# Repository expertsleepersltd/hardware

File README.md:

Please see individual folders for licensing information.

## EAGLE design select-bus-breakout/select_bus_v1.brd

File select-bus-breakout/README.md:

Select Bus Breakout
=====

https://www.expert-sleepers.co.uk/selectbusbreakout.html

Copyright (c) 2018 Expert Sleepers Ltd

Please refer to [LICENSE.md](LICENSE.md) for licensing information.

Please note that Expert Sleepers® is a registered trade mark in the UK. Remove any branding before making a derivative work.

Front panel layout is [here](../panels).

Board and schematic are in [EAGLE](https://en.wikipedia.org/wiki/EAGLE_(program)) format.

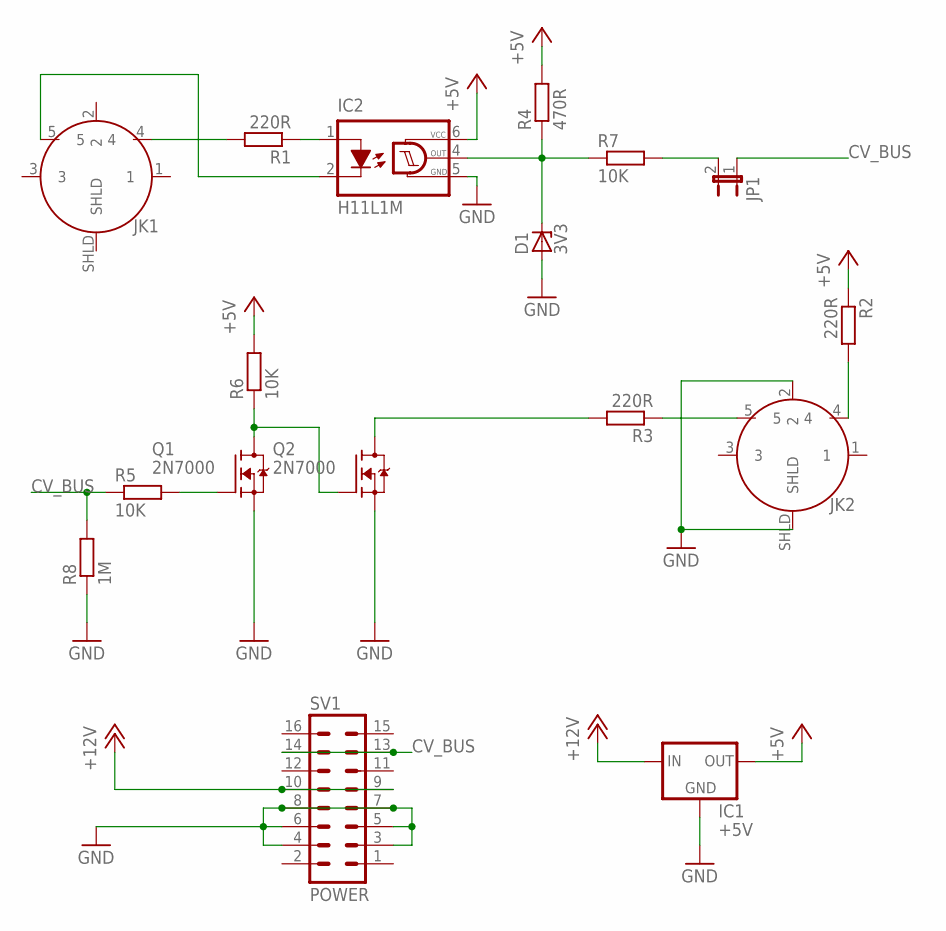
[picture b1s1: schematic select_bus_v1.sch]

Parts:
D1: 3V3; DO41Z10
IC1: +5V; 78LXX
IC2: H11L1M; DIL06
JK1, JK2: 13HP021PCB
JP1: JP1E; JP1
Q1, Q2: 2N7000; TO92
R1, R2, R3: 220R; 0207/10
R4: 470R; 0207/10
R5, R6: 10K; 0207/10
R7: 10K; 0207/2V
R8: 1M; 0207/10
SV1: POWER; ML16

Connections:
+5V: IC1.OUT, IC2.6 (VCC), R2.1, R4.2, R6.2
+12V: IC1.IN, SV1.9, SV1.10
CV_BUS: JP1.1, R5.1, R8.2, SV1.13, SV1.14
GND: D1.A, IC1.GND, IC2.5 (GND), JK2.2, JK2.SHLD, Q1.1 (S), Q2.1 (S), R8.1, SV1.3, SV1.4, SV1.5, SV1.6, SV1.7, SV1.8
unnamed: JP1.2, R7.2
unnamed: JK2.5, R3.1
unnamed: JK1.4, R1.2
unnamed: Q2.3 (D), R3.2
unnamed: JK2.4, R2.2
unnamed: IC2.1 (A), R1.1
unnamed: IC2.2 (C), JK1.5
unnamed: Q1.2 (G), R5.2
U1RX: D1.C, IC2.4 (OUT), R4.1, R7.1
U1TX: Q1.3 (D), Q2.2 (G), R6.1

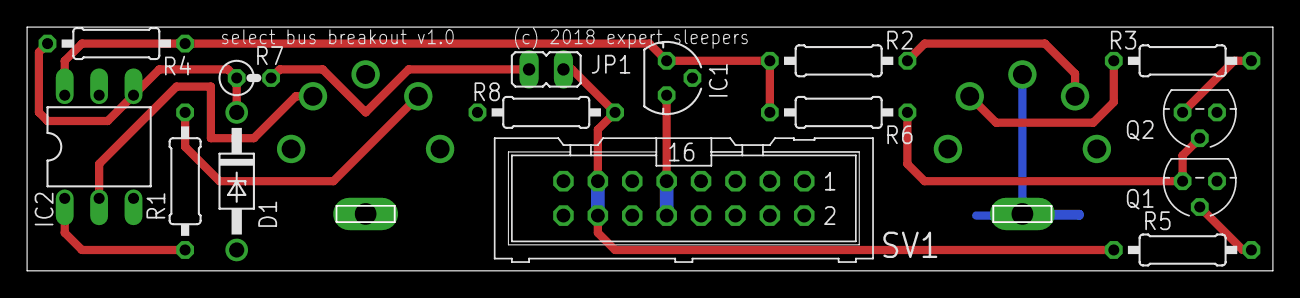
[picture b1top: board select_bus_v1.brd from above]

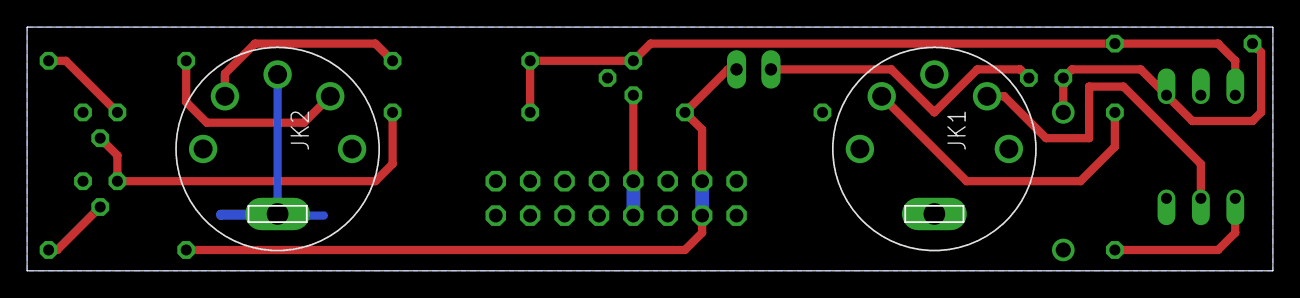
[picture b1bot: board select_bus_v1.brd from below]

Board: 2 copper layers, 91.9 x 17.9 mm, 17 parts (2 on the bottom side), 14 nets.

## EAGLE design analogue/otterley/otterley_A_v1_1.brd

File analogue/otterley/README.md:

Otterley
=====

https://expert-sleepers.co.uk/otterley.html

Copyright (c) 2024 Expert Sleepers Ltd

Please refer to [LICENSE.md](LICENSE.md) for licensing information.

Please note that Expert Sleepers® is a registered trade mark in the UK, the European Union, and the United States. Remove any branding before making a derivative work.

Front panel layout is [here](../../panels).

Board and schematic are in [EAGLE](https://en.wikipedia.org/wiki/EAGLE_(program)) format.

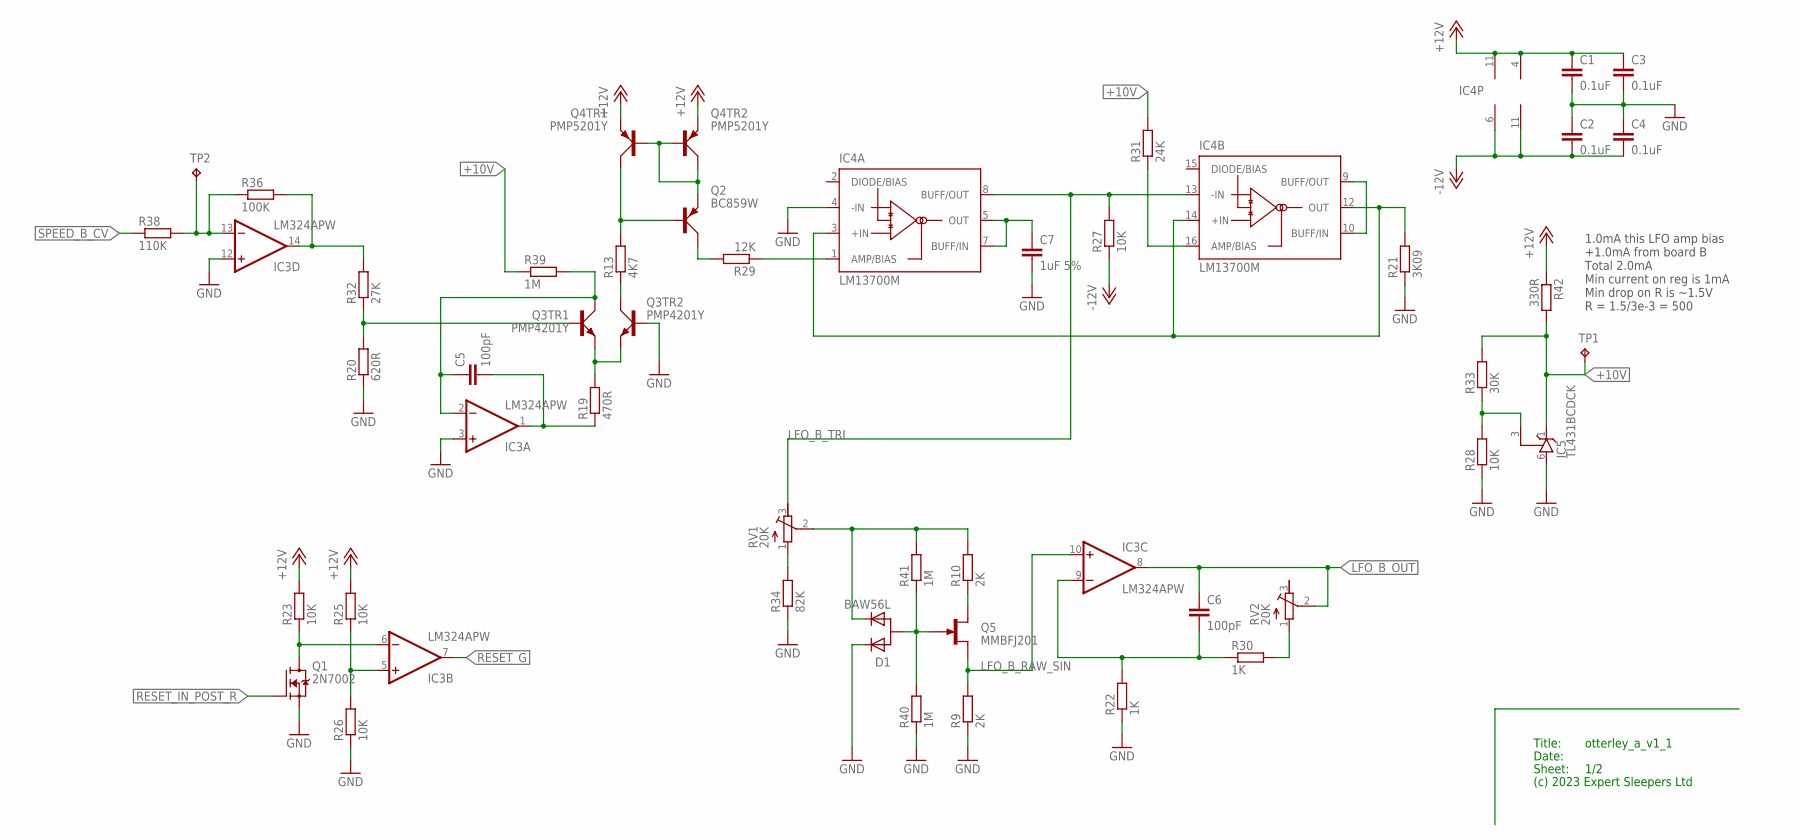
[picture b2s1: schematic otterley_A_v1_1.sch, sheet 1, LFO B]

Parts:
C1, C2, C3, C4: 0.1uF; C0402
C5, C6: 100pF; C0603
C7: 1uF 5%; C0805
D1: BAW56L; SOT-23
IC3: LM324APW; PW_R-PDSO-G14
IC4: LM13700M; SO16
IC5: TL431BCDCK; DCK_SC-70
Q1: 2N7002; SOT23
Q2: BC859W; SOT323
Q3: PMP4201Y; SOT65P210X110-6N
Q4: PMP5201Y; SOT65P210X110-6N
Q5: MMBFJ201; SOT23
R9, R10: 2K; R1206
R13: 4K7; R1206
R19: 470R; R1206
R20: 620R; R0603
R21: 3K09; R0603
R22, R30: 1K; R0603
R23, R25, R26, R27, R28: 10K; R0603
R29: 12K; R0603
R31: 24K; R0603
R32: 27K; R0603
R33: 30K; R0603
R34: 82K; R0603
R36: 100K; R0603
R38: 110K; R0603
R39, R40, R41: 1M; R0603
R42: 330R; R1206
RV1, RV2: 20K; 3306_W
TP1, TP2: RA2; P1-13

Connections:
+10V: IC5.1 (C), R31.2, R33.2, R39.1, R42.2, TP1.TP; also elsewhere on the board
+12V: C1.1, C3.1, IC3.4 (V+), IC4.11 (V+), Q4.4 (E), Q4.5 (E), R23.2, R25.2, R42.1; also elsewhere on the board
-12V: C2.2, C4.2, IC3.11 (V-), IC4.6 (V-), R27.1; also elsewhere on the board
GND: C1.2, C2.1, C3.2, C4.1, C7.2, D1.1 (C1), IC3.3 (+IN), IC3.12 (+IN), IC4.4 (-IN), IC5.6 (A), Q1.2 (S), Q3.2 (B), R9.1, R20.1, R21.1, R22.1, R26.1, R28.1, R34.1, R40.1; also elsewhere on the board
LFO_B_OUT: C6.1, IC3.8 (OUT), RV2.2 (S); also elsewhere on the board
LFO_B_RAW_SIN: IC3.10 (+IN), Q5.2 (S), R9.2
LFO_B_TRI: IC4.8 (BUFF/OUT), IC4.13 (-IN), R27.2, RV1.3 (E)
unnamed: IC5.3 (R), R28.2, R33.1
unnamed: IC3.6 (-IN), Q1.3 (D), R23.1
unnamed: IC3.5 (+IN), R25.1, R26.2
unnamed: IC3.14 (OUT), R32.2, R36.2
unnamed: IC4.9 (BUFF/OUT), IC4.10 (BUFF/IN)
unnamed: C7.1, IC4.5 (OUT), IC4.7 (BUFF/IN)
unnamed: IC4.3 (+IN), IC4.12 (OUT), IC4.14 (+IN), R21.2
unnamed: IC4.16 (AMP/BIAS), R31.1
unnamed: IC4.1 (AMP/BIAS), R29.1
unnamed: IC3.13 (-IN), R36.1, R38.2, TP2.TP
unnamed: C5.1, IC3.2 (-IN), Q3.6 (C), R39.2
unnamed: C5.2, IC3.1 (OUT), R19.1
unnamed: Q3.4 (E), Q3.5 (E), R19.2
unnamed: Q3.1 (B), R20.2, R32.1
unnamed: Q2.3 (C), R29.2
unnamed: Q2.1 (B), Q4.6 (C), R13.2
unnamed: Q2.2 (E), Q4.1 (B), Q4.2 (B), Q4.3 (C)
unnamed: Q3.3 (C), R13.1
unnamed: R34.2, RV1.1 (A)
unnamed: D1.2 (C2), R10.2, R41.2, RV1.2 (S)
unnamed: D1.3 (A), Q5.3 (G), R40.2, R41.1
unnamed: Q5.1 (D), R10.1
unnamed: C6.2, IC3.9 (-IN), R22.2, R30.1
unnamed: R30.2, RV2.1 (A)
RESET_G: IC3.7 (OUT); also elsewhere on the board
RESET_IN_POST_R: Q1.1 (G); also elsewhere on the board
SPEED_B_CV: R38.1; also elsewhere on the board

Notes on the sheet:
Title:
Date:
Sheet:
(c) 2023 Expert Sleepers Ltd
1.0mA this LFO amp bias +1.0mA from board B Total 2.0mA Min current on reg is 1mA Min drop on R is ~1.5V R = 1.5/3e-3 = 500

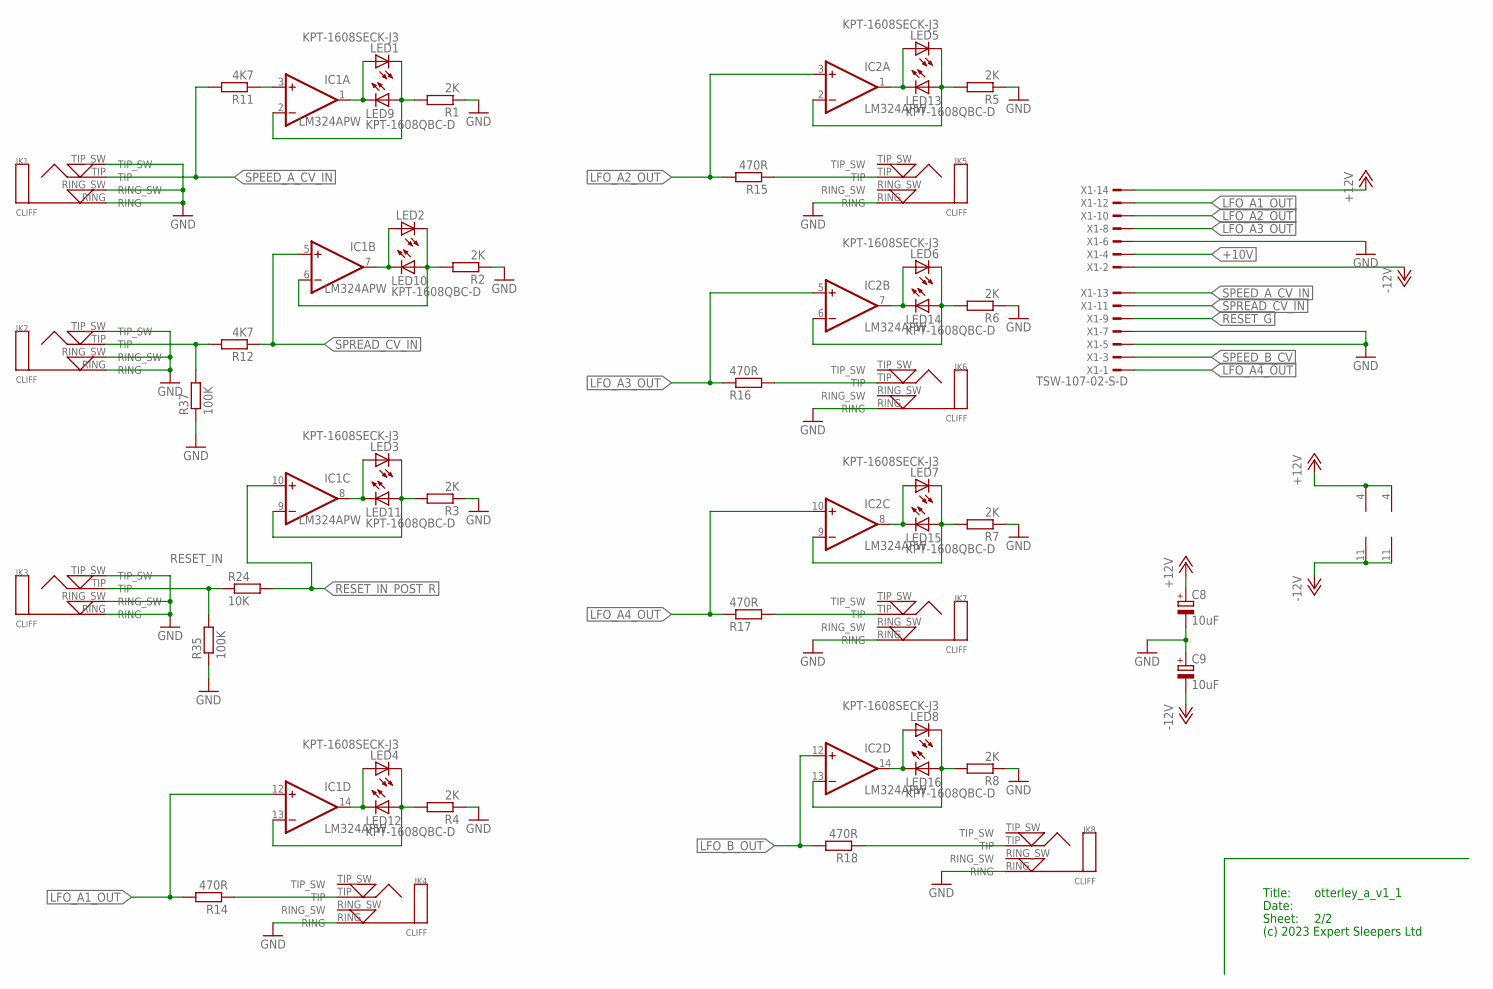
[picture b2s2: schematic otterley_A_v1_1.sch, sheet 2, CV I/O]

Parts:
C8, C9: 10uF; UD-4X5,8_NICHICON
IC1, IC2: LM324APW; PW_R-PDSO-G14
JK1, JK2, JK3, JK4, JK5, JK6, JK7, JK8: CLIFF; CLIFF3.5MMPCB
LED1, LED2, LED3, LED4, LED5, LED6, LED7, LED8: KPT-1608SECK-J3; CHIPLED_0603_LEFT
LED9, LED10, LED11, LED12, LED13, LED14, LED15, LED16: KPT-1608QBC-D; CHIPLED_0603_RIGHT
R1, R2, R3, R4, R5, R6, R7, R8: 2K; R1206
R11, R12: 4K7; R1206
R14, R15, R16, R17, R18: 470R; R1206
R24: 10K; R0603
R35, R37: 100K; R0603
X1: TSW-107-02-S-D

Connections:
+10V: X1.4; also elsewhere on the board
+12V: C8.+, IC1.4 (V+), IC2.4 (V+), X1.14; also elsewhere on the board
-12V: C9.-, IC1.11 (V-), IC2.11 (V-), X1.2; also elsewhere on the board
GND: C8.-, C9.+, JK1.RING, JK1.RING_SW, JK1.TIP_SW, JK2.RING, JK2.RING_SW, JK2.TIP_SW, JK3.RING, JK3.RING_SW, JK3.TIP_SW, JK4.RING, JK5.RING, JK6.RING, JK7.RING, JK8.RING, R1.1, R2.1, R3.1, R4.1, R5.1, R6.1, R7.1, R8.1, R35.1, R37.1, X1.5, X1.6, X1.7; also elsewhere on the board
LFO_A1_JACK: JK4.TIP, R14.1
LFO_A1_OUT: IC1.12 (+IN), R14.2, X1.12
LFO_A2_JACK: JK5.TIP, R15.1
LFO_A2_OUT: IC2.3 (+IN), R15.2, X1.10
LFO_A3_JACK: JK6.TIP, R16.2
LFO_A3_OUT: IC2.5 (+IN), R16.1, X1.8
LFO_A4_JACK: JK7.TIP, R17.2
LFO_A4_OUT: IC2.10 (+IN), R17.1, X1.1
LFO_B_JACK: JK8.TIP, R18.1
LFO_B_OUT: IC2.12 (+IN), R18.2; also elsewhere on the board
unnamed: IC1.13 (-IN), LED4.1 (C), LED12.1 (A), R4.2
unnamed: IC1.14 (OUT), LED4.2 (A), LED12.2 (C)
unnamed: IC2.2 (-IN), LED5.1 (C), LED13.1 (A), R5.2
unnamed: IC1.8 (OUT), LED3.2 (A), LED11.2 (C)
unnamed: JK2.TIP, R12.2, R37.2
unnamed: IC1.9 (-IN), LED3.1 (C), LED11.1 (A), R3.2
unnamed: IC1.1 (OUT), LED1.2 (A), LED9.2 (C)
unnamed: IC1.2 (-IN), LED1.1 (C), LED9.1 (A), R1.2
unnamed: IC1.3 (+IN), R11.1
unnamed: IC1.7 (OUT), LED2.2 (A), LED10.2 (C)
unnamed: IC1.6 (-IN), LED2.1 (C), LED10.1 (A), R2.2
unnamed: IC2.8 (OUT), LED7.2 (A), LED15.2 (C)
unnamed: IC2.9 (-IN), LED7.1 (C), LED15.1 (A), R7.2
unnamed: IC2.14 (OUT), LED8.2 (A), LED16.2 (C)
unnamed: IC2.13 (-IN), LED8.1 (C), LED16.1 (A), R8.2
unnamed: IC2.7 (OUT), LED6.2 (A), LED14.2 (C)
unnamed: IC2.6 (-IN), LED6.1 (C), LED14.1 (A), R6.2
unnamed: IC2.1 (OUT), LED5.2 (A), LED13.2 (C)
RESET_G: X1.9; also elsewhere on the board
RESET_IN: JK3.TIP, R24.1, R35.2
RESET_IN_POST_R: IC1.10 (+IN), R24.2; also elsewhere on the board
SPEED_A_CV_IN: JK1.TIP, R11.2, X1.13
SPEED_B_CV: X1.3; also elsewhere on the board
SPREAD_CV_IN: IC1.5 (+IN), R12.1, X1.11

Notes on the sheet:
Title:
Date:
Sheet:
(c) 2023 Expert Sleepers Ltd

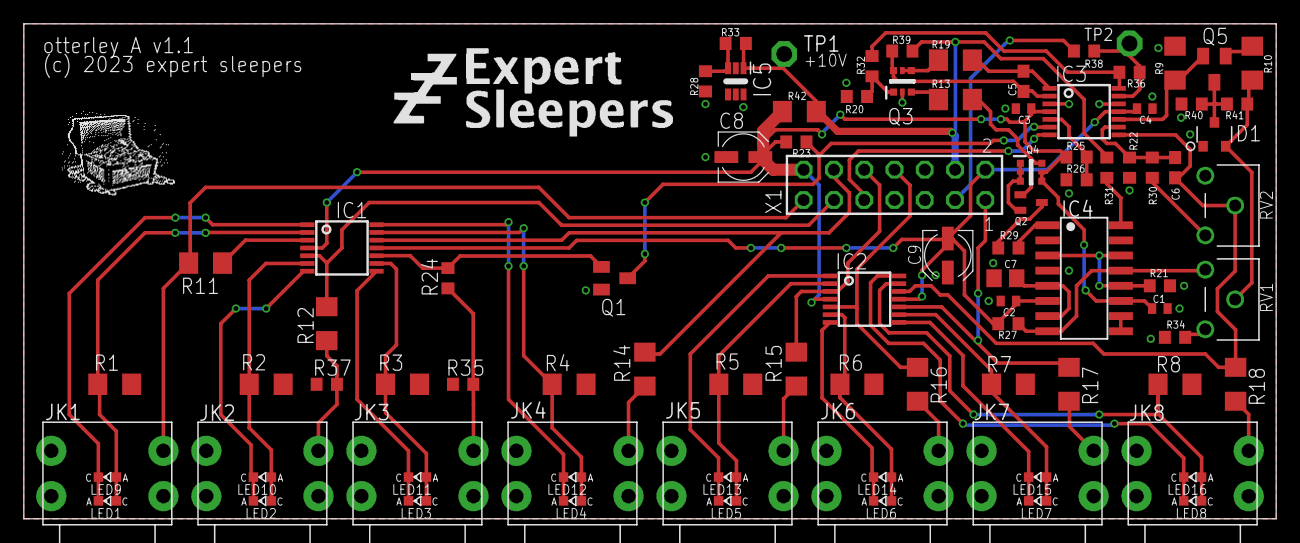
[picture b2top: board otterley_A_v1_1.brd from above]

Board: 2 copper layers, 105.0 x 41.5 mm, 93 parts (0 on the bottom side), 64 nets.

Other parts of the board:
U$1: ES_ZZZ_TEXT_TPLACE_1IN_600DPI
U$2: TREASURE_10MM_300DPI

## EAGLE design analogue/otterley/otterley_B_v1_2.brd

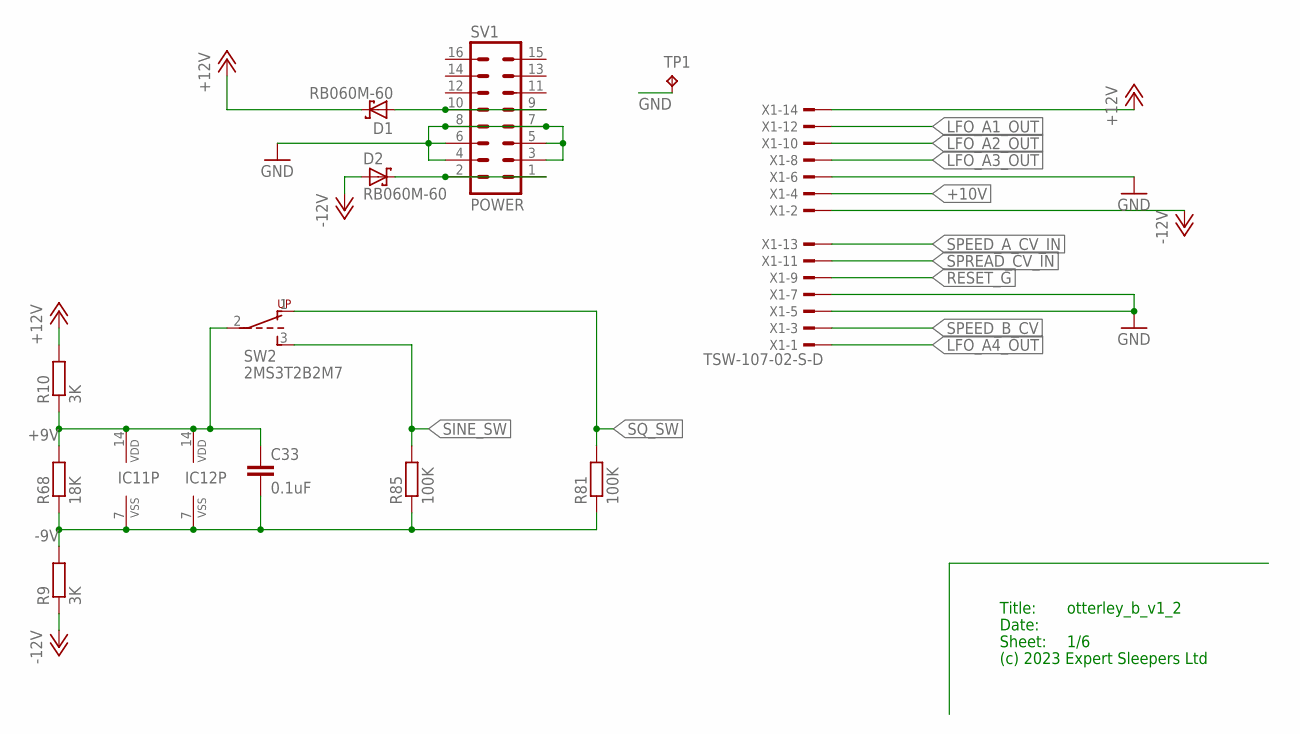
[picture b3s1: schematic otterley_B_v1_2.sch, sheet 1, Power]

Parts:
C33: 0.1uF; C0402
D1, D2: RB060M-60; SOD123FL
IC11, IC12: CD4066BPW; PW_R-PDSO-G14
R9, R10: 3K; R0603
R68: 18K; R0603
R81, R85: 100K; R0603
SV1: POWER; ML16
SW2: 2MS3T2B2M7; 2MS1T2B2M7RE
TP1: RA2; P1-13
X1: TSW-107-02-S-D

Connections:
+9V: C33.1, IC11.14 (VDD), IC12.14 (VDD), R10.1, R68.2, SW2.2 (PR)
+10V: X1.4; also elsewhere on the board
+12V: D1.C, R10.2, X1.14; also elsewhere on the board
-9V: C33.2, IC11.7 (VSS), IC12.7 (VSS), R9.2, R68.1, R81.1, R85.1
-12V: D2.A, R9.1, X1.2; also elsewhere on the board
GND: SV1.3, SV1.4, SV1.5, SV1.6, SV1.7, SV1.8, TP1.TP, X1.5, X1.6, X1.7; also elsewhere on the board
LFO_A1_OUT: X1.12; also elsewhere on the board
LFO_A2_OUT: X1.10; also elsewhere on the board
LFO_A3_OUT: X1.8; also elsewhere on the board
LFO_A4_OUT: X1.1; also elsewhere on the board
unnamed: D2.C, SV1.1, SV1.2
unnamed: D1.A, SV1.9, SV1.10
RESET_G: X1.9; also elsewhere on the board
SINE_SW: R85.2, SW2.3 (RD); also elsewhere on the board
SPEED_A_CV_IN: X1.13; also elsewhere on the board
SPEED_B_CV: X1.3; also elsewhere on the board
SPREAD_CV_IN: X1.11; also elsewhere on the board
SQ_SW: R81.2, SW2.1 (RU); also elsewhere on the board

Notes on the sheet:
Title:
Date:
Sheet:
(c) 2023 Expert Sleepers Ltd

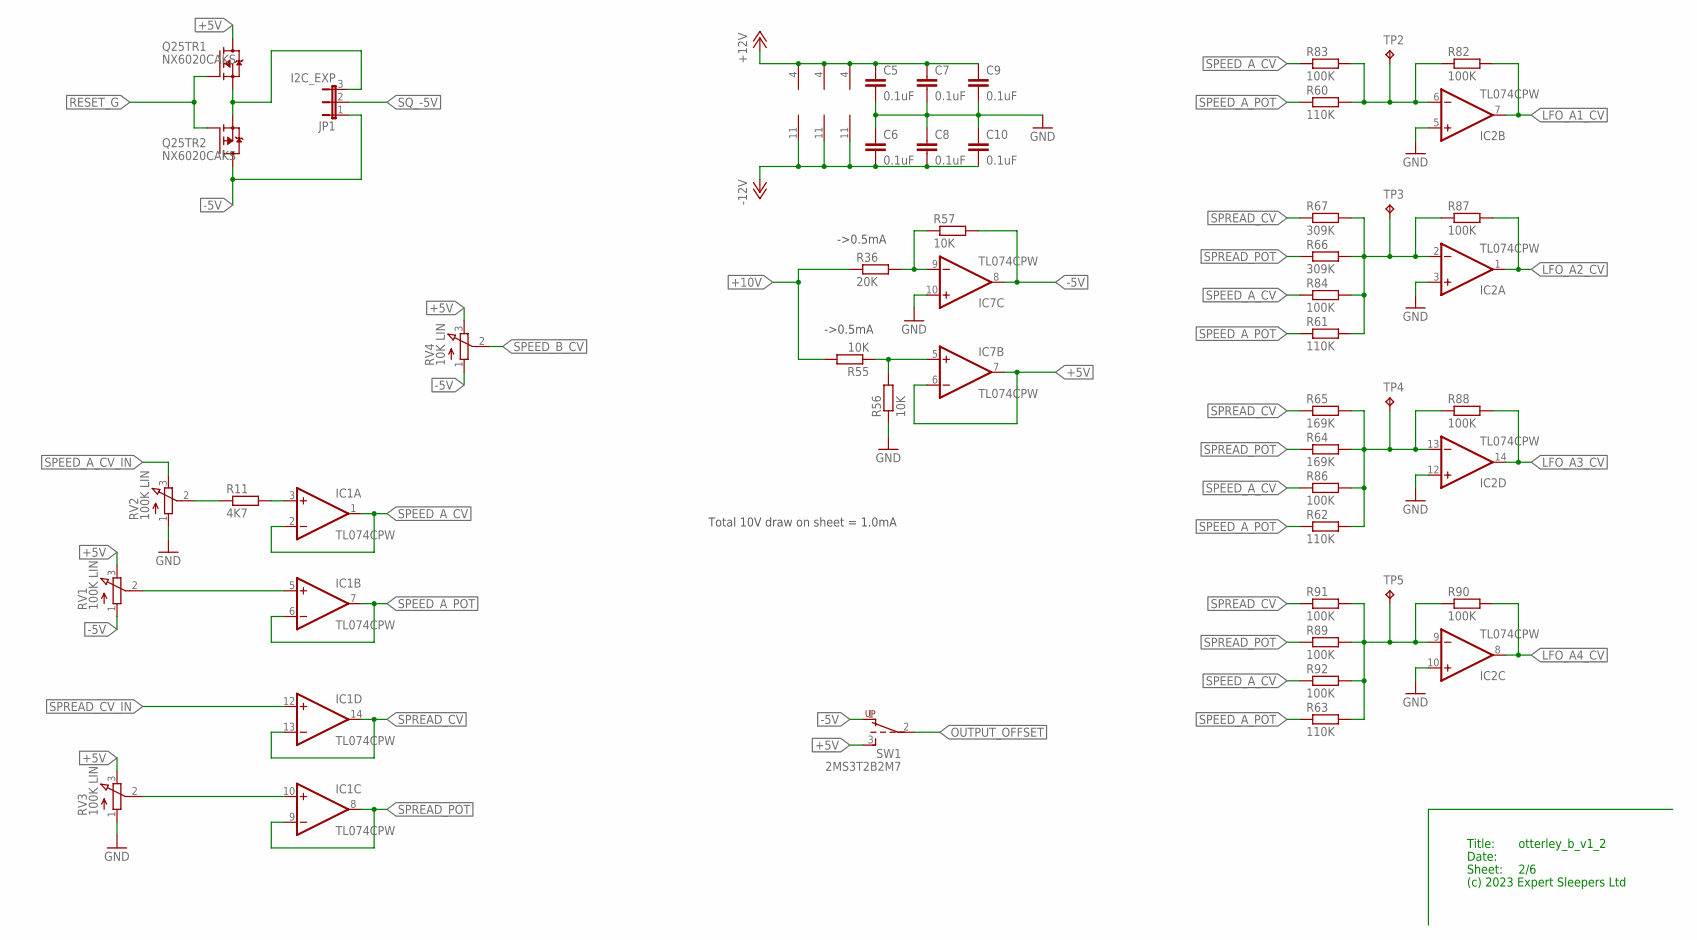
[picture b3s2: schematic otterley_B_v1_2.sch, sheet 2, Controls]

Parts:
C5, C6, C7, C8, C9, C10: 0.1uF; C0402
IC1, IC2, IC7: TL074CPW; PW_R-PDSO-G14
JP1: I2C_EXP; JP2
Q25: NX6020CAKS; SOT363
R11: 4K7; R0603
R36: 20K; R0603
R55, R56, R57: 10K; R0603
R60, R61, R62, R63: 110K; R0603
R64, R65: 169K; R0603
R66, R67: 309K; R0603
R82, R83, R84, R86, R87, R88, R89, R90, R91, R92: 100K; R0603
RV1, RV2, RV3: 100K LIN; RD1610NOA0X
RV4: 10K LIN; RD1610NOA0X
SW1: 2MS3T2B2M7; 2MS1T2B2M7RE
TP2, TP3, TP4, TP5: RA2; P1-13

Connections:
+5V: IC7.6 (-IN), IC7.7 (OUT), Q25.6 (D), RV1.3 (E), RV3.3 (E), RV4.3 (E), SW1.3 (RD); also elsewhere on the board
+10V: R36.1, R55.2; also elsewhere on the board
+12V: C5.1, C7.1, C9.1, IC1.4 (V+), IC2.4 (V+), IC7.4 (V+); also elsewhere on the board
-5V: IC7.8 (OUT), JP1.1, Q25.3 (D), R57.2, RV1.1 (A), RV4.1 (A), SW1.1 (RU)
-12V: C6.2, C8.2, C10.2, IC1.11 (V-), IC2.11 (V-), IC7.11 (V-); also elsewhere on the board
GND: C5.2, C6.1, C7.2, C8.1, C9.2, C10.1, IC2.3 (+IN), IC2.5 (+IN), IC2.10 (+IN), IC2.12 (+IN), IC7.10 (+IN), R56.1, RV2.1 (A), RV3.1 (A); also elsewhere on the board
LFO_A1_CV: IC2.7 (OUT), R82.2; also elsewhere on the board
LFO_A2_CV: IC2.1 (OUT), R87.2; also elsewhere on the board
LFO_A3_CV: IC2.14 (OUT), R88.2; also elsewhere on the board
LFO_A4_CV: IC2.8 (OUT), R90.2; also elsewhere on the board
unnamed: JP1.3, Q25.1 (S), Q25.4 (S)
unnamed: IC1.5 (+IN), RV1.2 (S)
unnamed: R11.1, RV2.2 (S)
unnamed: IC7.5 (+IN), R55.1, R56.2
unnamed: IC7.9 (-IN), R36.2, R57.1
unnamed: IC2.2 (-IN), R61.2, R66.2, R67.2, R84.2, R87.1, TP3.TP
unnamed: IC1.3 (+IN), R11.2
unnamed: IC2.6 (-IN), R60.2, R82.1, R83.2, TP2.TP
unnamed: IC1.10 (+IN), RV3.2 (S)
unnamed: IC2.13 (-IN), R62.2, R64.2, R65.2, R86.2, R88.1, TP4.TP
unnamed: IC2.9 (-IN), R63.2, R89.2, R90.1, R91.2, R92.2, TP5.TP
OUTPUT_OFFSET: SW1.2 (PR); also elsewhere on the board
RESET_G: Q25.2 (G), Q25.5 (G); also elsewhere on the board
SPEED_A_CV: IC1.1 (OUT), IC1.2 (-IN), R83.1, R84.1, R86.1, R92.1
SPEED_A_CV_IN: RV2.3 (E); also elsewhere on the board
SPEED_A_POT: IC1.6 (-IN), IC1.7 (OUT), R60.1, R61.1, R62.1, R63.1
SPEED_B_CV: RV4.2 (S); also elsewhere on the board
SPREAD_CV: IC1.13 (-IN), IC1.14 (OUT), R65.1, R67.1, R91.1
SPREAD_CV_IN: IC1.12 (+IN); also elsewhere on the board
SPREAD_POT: IC1.8 (OUT), IC1.9 (-IN), R64.1, R66.1, R89.1
SQ_-5V: JP1.2; also elsewhere on the board

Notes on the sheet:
Title:
Date:
Sheet:
(c) 2023 Expert Sleepers Ltd
->0.5mA
Total 10V draw on sheet = 1.0mA

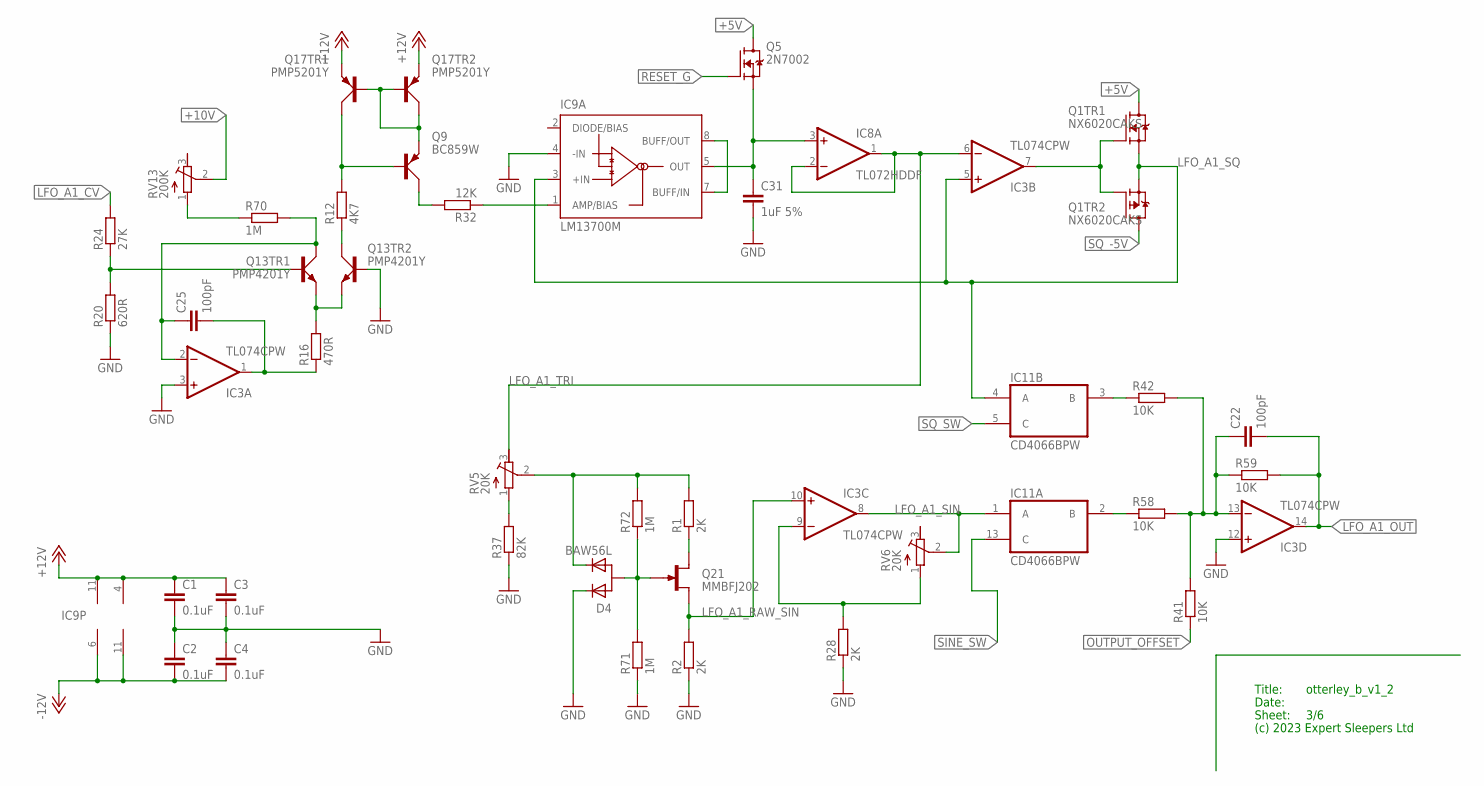
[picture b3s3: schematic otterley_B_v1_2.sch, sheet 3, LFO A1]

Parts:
C1, C2, C3, C4: 0.1uF; C0402
C22, C25: 100pF; C0603
C31: 1uF 5%; C0805
D4: BAW56L; SOT-23
IC3: TL074CPW; PW_R-PDSO-G14
IC8: TL072HDDF; DDF0008A
IC9: LM13700M; SO16
IC11: CD4066BPW; PW_R-PDSO-G14
Q1: NX6020CAKS; SOT363
Q5: 2N7002; SOT23
Q9: BC859W; SOT323
Q13: PMP4201Y; SOT65P210X110-6N
Q17: PMP5201Y; SOT65P210X110-6N
Q21: MMBFJ202; SOT23
R1, R2, R28: 2K; R0603
R12: 4K7; R0603
R16: 470R; R0603
R20: 620R; R0603
R24: 27K; R0603
R32: 12K; R0603
R37: 82K; R0603
R41, R42, R58, R59: 10K; R0603
R70, R71, R72: 1M; R0603
RV5, RV6: 20K; TC33X
RV13: 200K; TC33X

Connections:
+5V: Q1.6 (D), Q5.3 (D); also elsewhere on the board
+10V: RV13.2 (S); also elsewhere on the board
+12V: C1.1, C3.1, IC3.4 (V+), IC9.11 (V+), Q17.4 (E), Q17.5 (E); also elsewhere on the board
-12V: C2.2, C4.2, IC3.11 (V-), IC9.6 (V-); also elsewhere on the board
GND: C1.2, C2.1, C3.2, C4.1, C31.2, D4.1 (C1), IC3.3 (+IN), IC3.12 (+IN), IC9.4 (-IN), Q13.2 (B), R2.1, R20.1, R28.1, R37.1, R71.1; also elsewhere on the board
LFO_A1_CV: R24.2; also elsewhere on the board
LFO_A1_OUT: C22.2, IC3.14 (OUT), R59.2; also elsewhere on the board
LFO_A1_RAW_SIN: IC3.10 (+IN), Q21.2 (S), R2.2
LFO_A1_SIN: IC3.8 (OUT), IC11.1 (A), RV6.2 (S)
LFO_A1_SQ: IC3.5 (+IN), IC9.3 (+IN), IC11.4 (A), Q1.1 (S), Q1.4 (S)
LFO_A1_TRI: IC3.6 (-IN), IC8.1 (OUT), IC8.2 (-IN), RV5.3 (E)
unnamed: IC9.7 (BUFF/IN), IC9.8 (BUFF/OUT)
unnamed: IC11.3 (B), R42.1
unnamed: C31.1, IC8.3 (+IN), IC9.5 (OUT), Q5.2 (S)
unnamed: IC9.1 (AMP/BIAS), R32.1
unnamed: C25.1, IC3.2 (-IN), Q13.6 (C), R70.2
unnamed: C25.2, IC3.1 (OUT), R16.1
unnamed: Q13.4 (E), Q13.5 (E), R16.2
unnamed: Q9.3 (C), R32.2
unnamed: Q13.3 (C), R12.1
unnamed: Q9.1 (B), Q17.6 (C), R12.2
unnamed: Q9.2 (E), Q17.1 (B), Q17.2 (B), Q17.3 (C)
unnamed: IC3.9 (-IN), R28.2, RV6.1 (A)
unnamed: R37.2, RV5.1 (A)
unnamed: D4.2 (C2), R1.2, R72.2, RV5.2 (S)
unnamed: D4.3 (A), Q21.3 (G), R71.2, R72.1
unnamed: C22.1, IC3.13 (-IN), R41.2, R42.2, R58.2, R59.1
unnamed: Q21.1 (D), R1.1
unnamed: IC11.2 (B), R58.1
unnamed: R70.1, RV13.1 (A)
unnamed: Q13.1 (B), R20.2, R24.1
unnamed: IC3.7 (OUT), Q1.2 (G), Q1.5 (G)
OUTPUT_OFFSET: R41.1; also elsewhere on the board
RESET_G: Q5.1 (G); also elsewhere on the board
SINE_SW: IC11.13 (C); also elsewhere on the board
SQ_-5V: Q1.3 (D); also elsewhere on the board
SQ_SW: IC11.5 (C); also elsewhere on the board

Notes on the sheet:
Title:
Date:
Sheet:
(c) 2023 Expert Sleepers Ltd

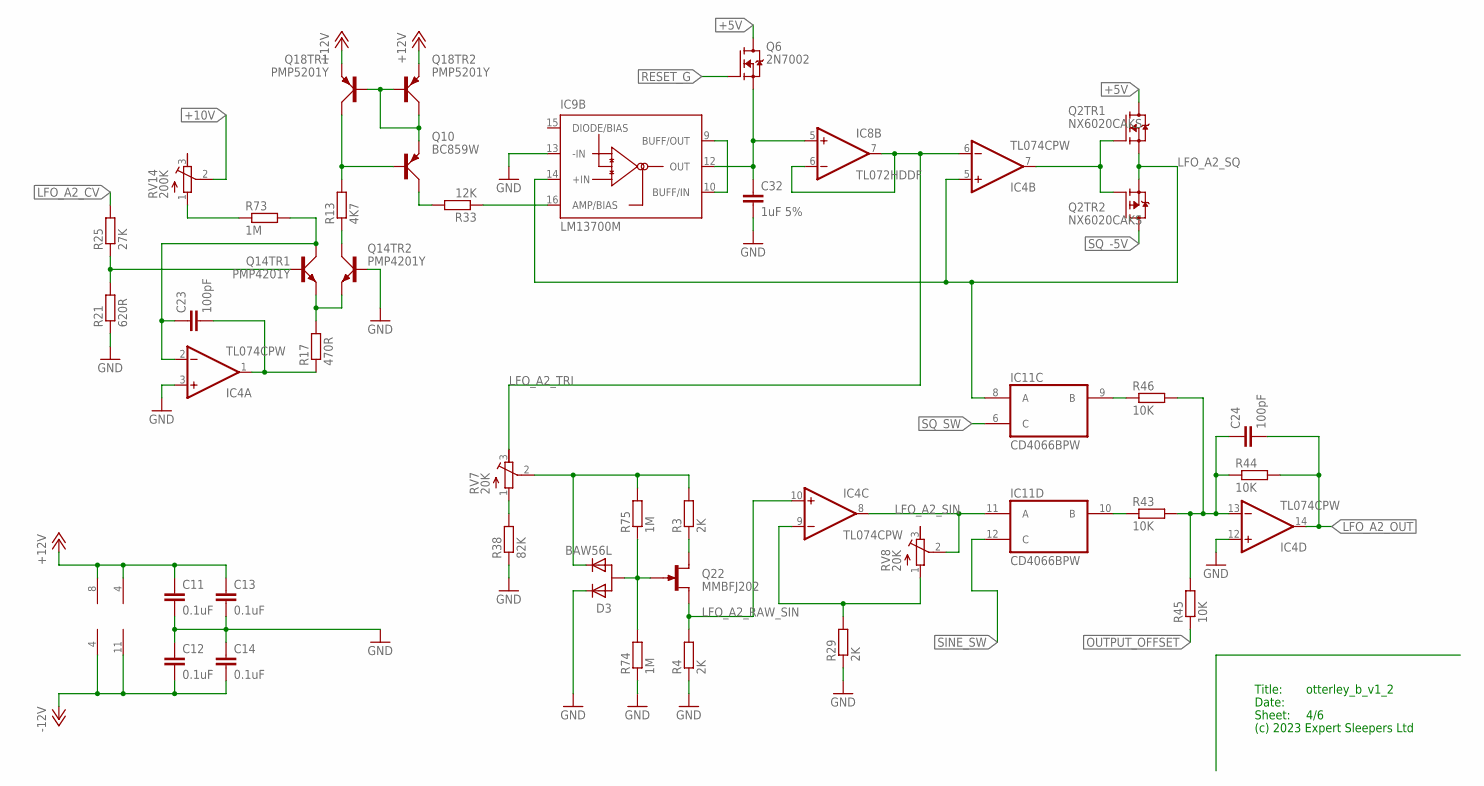
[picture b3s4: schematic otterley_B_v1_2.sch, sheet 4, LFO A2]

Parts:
C11, C12, C13, C14: 0.1uF; C0402
C23, C24: 100pF; C0603
C32: 1uF 5%; C0805
D3: BAW56L; SOT-23
IC4: TL074CPW; PW_R-PDSO-G14
IC8: TL072HDDF; DDF0008A
IC9: LM13700M; SO16
IC11: CD4066BPW; PW_R-PDSO-G14
Q2: NX6020CAKS; SOT363
Q6: 2N7002; SOT23
Q10: BC859W; SOT323
Q14: PMP4201Y; SOT65P210X110-6N
Q18: PMP5201Y; SOT65P210X110-6N
Q22: MMBFJ202; SOT23
R3, R4, R29: 2K; R0603
R13: 4K7; R0603
R17: 470R; R0603
R21: 620R; R0603
R25: 27K; R0603
R33: 12K; R0603
R38: 82K; R0603
R43, R44, R45, R46: 10K; R0603
R73, R74, R75: 1M; R0603
RV7, RV8: 20K; TC33X
RV14: 200K; TC33X

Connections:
+5V: Q2.6 (D), Q6.3 (D); also elsewhere on the board
+10V: RV14.2 (S); also elsewhere on the board
+12V: C11.1, C13.1, IC4.4 (V+), IC8.8 (V+), Q18.4 (E), Q18.5 (E); also elsewhere on the board
-12V: C12.2, C14.2, IC4.11 (V-), IC8.4 (V-); also elsewhere on the board
GND: C11.2, C12.1, C13.2, C14.1, C32.2, D3.1 (C1), IC4.3 (+IN), IC4.12 (+IN), IC9.13 (-IN), Q14.2 (B), R4.1, R21.1, R29.1, R38.1, R74.1; also elsewhere on the board
LFO_A2_CV: R25.2; also elsewhere on the board
LFO_A2_OUT: C24.2, IC4.14 (OUT), R44.2; also elsewhere on the board
LFO_A2_RAW_SIN: IC4.10 (+IN), Q22.2 (S), R4.2
LFO_A2_SIN: IC4.8 (OUT), IC11.11 (A), RV8.2 (S)
LFO_A2_SQ: IC4.5 (+IN), IC9.14 (+IN), IC11.8 (A), Q2.1 (S), Q2.4 (S)
LFO_A2_TRI: IC4.6 (-IN), IC8.6 (-IN), IC8.7 (OUT), RV7.3 (E)
unnamed: IC11.9 (B), R46.1
unnamed: IC9.9 (BUFF/OUT), IC9.10 (BUFF/IN)
unnamed: C32.1, IC8.5 (+IN), IC9.12 (OUT), Q6.2 (S)
unnamed: IC9.16 (AMP/BIAS), R33.1
unnamed: C23.1, IC4.2 (-IN), Q14.6 (C), R73.2
unnamed: C23.2, IC4.1 (OUT), R17.1
unnamed: Q14.4 (E), Q14.5 (E), R17.2
unnamed: Q10.3 (C), R33.2
unnamed: Q10.1 (B), Q18.6 (C), R13.2
unnamed: Q10.2 (E), Q18.1 (B), Q18.2 (B), Q18.3 (C)
unnamed: Q14.3 (C), R13.1
unnamed: R38.2, RV7.1 (A)
unnamed: D3.2 (C2), R3.2, R75.2, RV7.2 (S)
unnamed: D3.3 (A), Q22.3 (G), R74.2, R75.1
unnamed: Q22.1 (D), R3.1
unnamed: IC4.9 (-IN), R29.2, RV8.1 (A)
unnamed: C24.1, IC4.13 (-IN), R43.2, R44.1, R45.2, R46.2
unnamed: IC4.7 (OUT), Q2.2 (G), Q2.5 (G)
unnamed: IC11.10 (B), R43.1
unnamed: R73.1, RV14.1 (A)
unnamed: Q14.1 (B), R21.2, R25.1
OUTPUT_OFFSET: R45.1; also elsewhere on the board
RESET_G: Q6.1 (G); also elsewhere on the board
SINE_SW: IC11.12 (C); also elsewhere on the board
SQ_-5V: Q2.3 (D); also elsewhere on the board
SQ_SW: IC11.6 (C); also elsewhere on the board

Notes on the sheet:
Title:
Date:
Sheet:
(c) 2023 Expert Sleepers Ltd

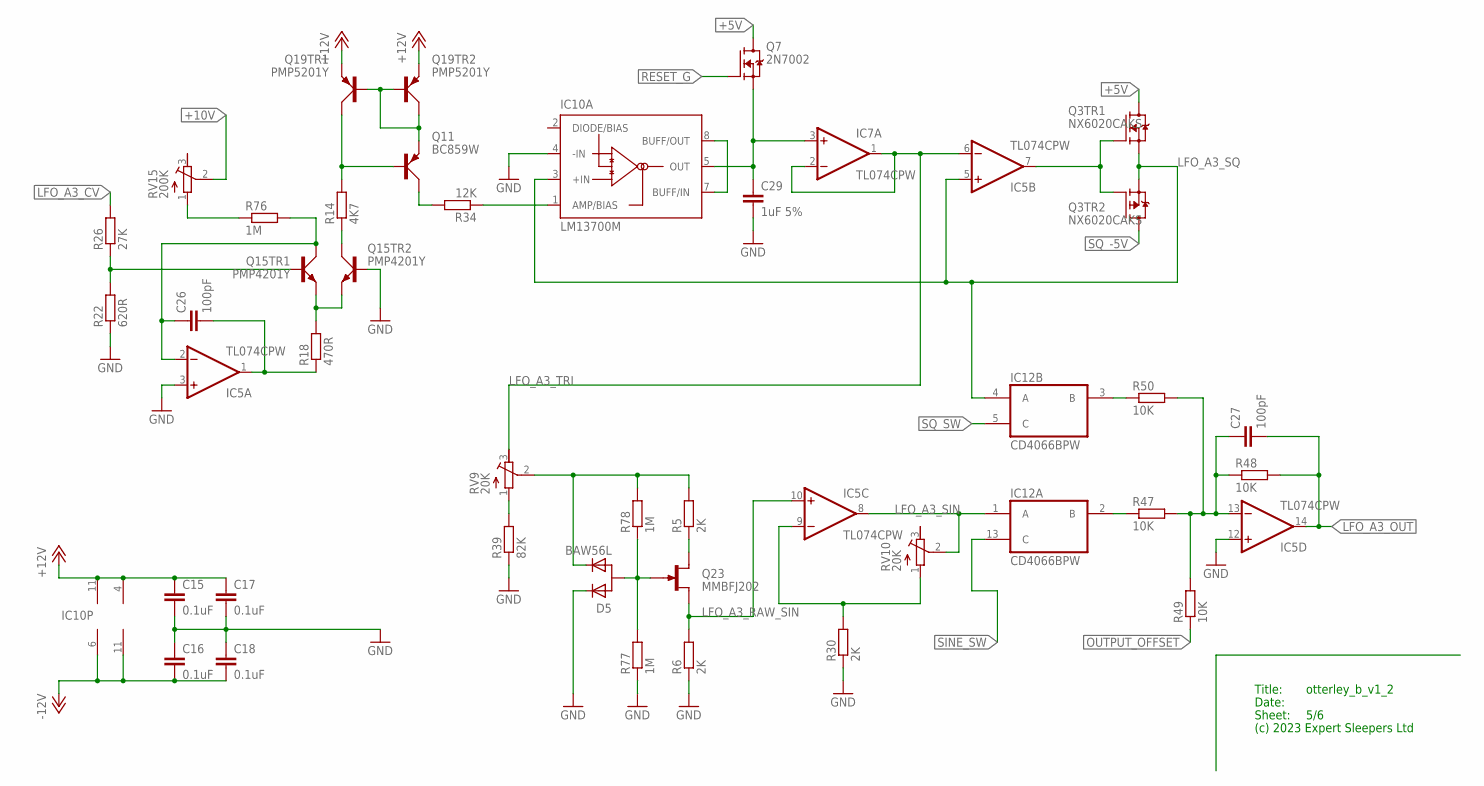
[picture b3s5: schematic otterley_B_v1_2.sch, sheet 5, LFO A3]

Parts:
C15, C16, C17, C18: 0.1uF; C0402
C26, C27: 100pF; C0603
C29: 1uF 5%; C0805
D5: BAW56L; SOT-23
IC5, IC7: TL074CPW; PW_R-PDSO-G14
IC10: LM13700M; SO16
IC12: CD4066BPW; PW_R-PDSO-G14
Q3: NX6020CAKS; SOT363
Q7: 2N7002; SOT23
Q11: BC859W; SOT323
Q15: PMP4201Y; SOT65P210X110-6N
Q19: PMP5201Y; SOT65P210X110-6N
Q23: MMBFJ202; SOT23
R5, R6, R30: 2K; R0603
R14: 4K7; R0603
R18: 470R; R0603
R22: 620R; R0603
R26: 27K; R0603
R34: 12K; R0603
R39: 82K; R0603
R47, R48, R49, R50: 10K; R0603
R76, R77, R78: 1M; R0603
RV9, RV10: 20K; TC33X
RV15: 200K; TC33X

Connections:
+5V: Q3.6 (D), Q7.3 (D); also elsewhere on the board
+10V: RV15.2 (S); also elsewhere on the board
+12V: C15.1, C17.1, IC5.4 (V+), IC10.11 (V+), Q19.4 (E), Q19.5 (E); also elsewhere on the board
-12V: C16.2, C18.2, IC5.11 (V-), IC10.6 (V-); also elsewhere on the board
GND: C15.2, C16.1, C17.2, C18.1, C29.2, D5.1 (C1), IC5.3 (+IN), IC5.12 (+IN), IC10.4 (-IN), Q15.2 (B), R6.1, R22.1, R30.1, R39.1, R77.1; also elsewhere on the board
LFO_A3_CV: R26.2; also elsewhere on the board
LFO_A3_OUT: C27.2, IC5.14 (OUT), R48.2; also elsewhere on the board
LFO_A3_RAW_SIN: IC5.10 (+IN), Q23.2 (S), R6.2
LFO_A3_SIN: IC5.8 (OUT), IC12.1 (A), RV10.2 (S)
LFO_A3_SQ: IC5.5 (+IN), IC10.3 (+IN), IC12.4 (A), Q3.1 (S), Q3.4 (S)
LFO_A3_TRI: IC5.6 (-IN), IC7.1 (OUT), IC7.2 (-IN), RV9.3 (E)
unnamed: IC10.7 (BUFF/IN), IC10.8 (BUFF/OUT)
unnamed: IC12.3 (B), R50.1
unnamed: C29.1, IC7.3 (+IN), IC10.5 (OUT), Q7.2 (S)
unnamed: IC10.1 (AMP/BIAS), R34.1
unnamed: C26.1, IC5.2 (-IN), Q15.6 (C), R76.2
unnamed: C26.2, IC5.1 (OUT), R18.1
unnamed: Q15.4 (E), Q15.5 (E), R18.2
unnamed: Q11.3 (C), R34.2
unnamed: Q11.1 (B), Q19.6 (C), R14.2
unnamed: Q11.2 (E), Q19.1 (B), Q19.2 (B), Q19.3 (C)
unnamed: Q15.3 (C), R14.1
unnamed: R39.2, RV9.1 (A)
unnamed: D5.2 (C2), R5.2, R78.2, RV9.2 (S)
unnamed: D5.3 (A), Q23.3 (G), R77.2, R78.1
unnamed: Q23.1 (D), R5.1
unnamed: IC5.9 (-IN), R30.2, RV10.1 (A)
unnamed: C27.1, IC5.13 (-IN), R47.2, R48.1, R49.2, R50.2
unnamed: IC5.7 (OUT), Q3.2 (G), Q3.5 (G)
unnamed: IC12.2 (B), R47.1
unnamed: R76.1, RV15.1 (A)
unnamed: Q15.1 (B), R22.2, R26.1
OUTPUT_OFFSET: R49.1; also elsewhere on the board
RESET_G: Q7.1 (G); also elsewhere on the board
SINE_SW: IC12.13 (C); also elsewhere on the board
SQ_-5V: Q3.3 (D); also elsewhere on the board
SQ_SW: IC12.5 (C); also elsewhere on the board

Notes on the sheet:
Title:
Date:
Sheet:
(c) 2023 Expert Sleepers Ltd
